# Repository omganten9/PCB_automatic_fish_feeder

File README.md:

# IoT-Based Automatic Fish Feeder System 🐟

An **IoT-integrated automatic fish feeder** designed using **ESP32** and **KiCad PCB design** to optimize aquarium maintenance.  
This project was developed as part of the *Final Project RE 2* course at Universitas Indonesia (2023).

---

## 🧠 Overview
This system enables automated and remote control of fish feeding using IoT technology.  
With motion and turbidity sensors, the feeder intelligently manages feeding schedules, monitors water conditions, and communicates through a **web server** via **Wi-Fi**.

**Key features:**
- Remote feeding schedule control via web interface  
- Real-time water turbidity monitoring  
- OLED/LCD display showing feeding status and last feeding time  
- Owner confirmation before auto-feeding for security  
- Deep sleep mode for efficient power usage  

---

## ⚙️ Hardware Summary
- **Microcontroller:** ESP32  
- **Sensors:** PIR (motion) sensor, turbidity sensor  
- **Actuators:** Servo motor (feeding mechanism), buzzer  
- **Display:** OLED / LCD  
- **Power System:** TP4056 Li-Ion charger module, 3.7V Li-ion battery  
- **Interfaces:** UART, USB Type-C (CP2104), Wi-Fi (Web Server)  

---

## 🧩 PCB Design
The PCB was designed using **KiCad** with:
- Dual-layer copper traces (signal + ground)  
- Ground filling for noise reduction and EMI suppression  
- Proper antenna clearance for ESP32 Wi-Fi module  
- Mounting holes for mechanical stability  
- Compact design for integration inside an aquarium enclosure  

---

## 🧰 Components Used
| Category | Components |
|-----------|-------------|
| Microcontroller | ESP32 |
| Sensors | PIR, Turbidity Sensor |
| Display | OLED/LCD |
| Actuators | Servo Motor, Buzzer |
| Power | TP4056, Li-ion Battery |
| Communication | CP2104 USB to UART, Wi-Fi |

---

## 📐 PCB Layout (Example)  

---

## 🧾 Author & Contribution
**Team 8 – Final Project RE 2 (Universitas Indonesia, 2023)**  
- **M. Akmal Prabowo** – Schematic & PCB Design, Report (Results & Discussion)  
- **M. Daffa Zainal** – Schematic Documentation  
- **Salman Hakim Kurnia** – Feature & Component Design, Ideation, Video Editing  

---

## 📚 Reference
Full report: *Final Project RE 2 – IoT-Based Automatic Fish Feeder System (Universitas Indonesia, 2023)*  
YouTube Demo: [https://www.youtube.com/watch?v=FHcyZINsoDI](https://www.youtube.com/watch?v=FHcyZINsoDI)

---

## 📜 License
This project is for **educational and personal portfolio use only**.  
Commercial reproduction or redistribution is not permitted.

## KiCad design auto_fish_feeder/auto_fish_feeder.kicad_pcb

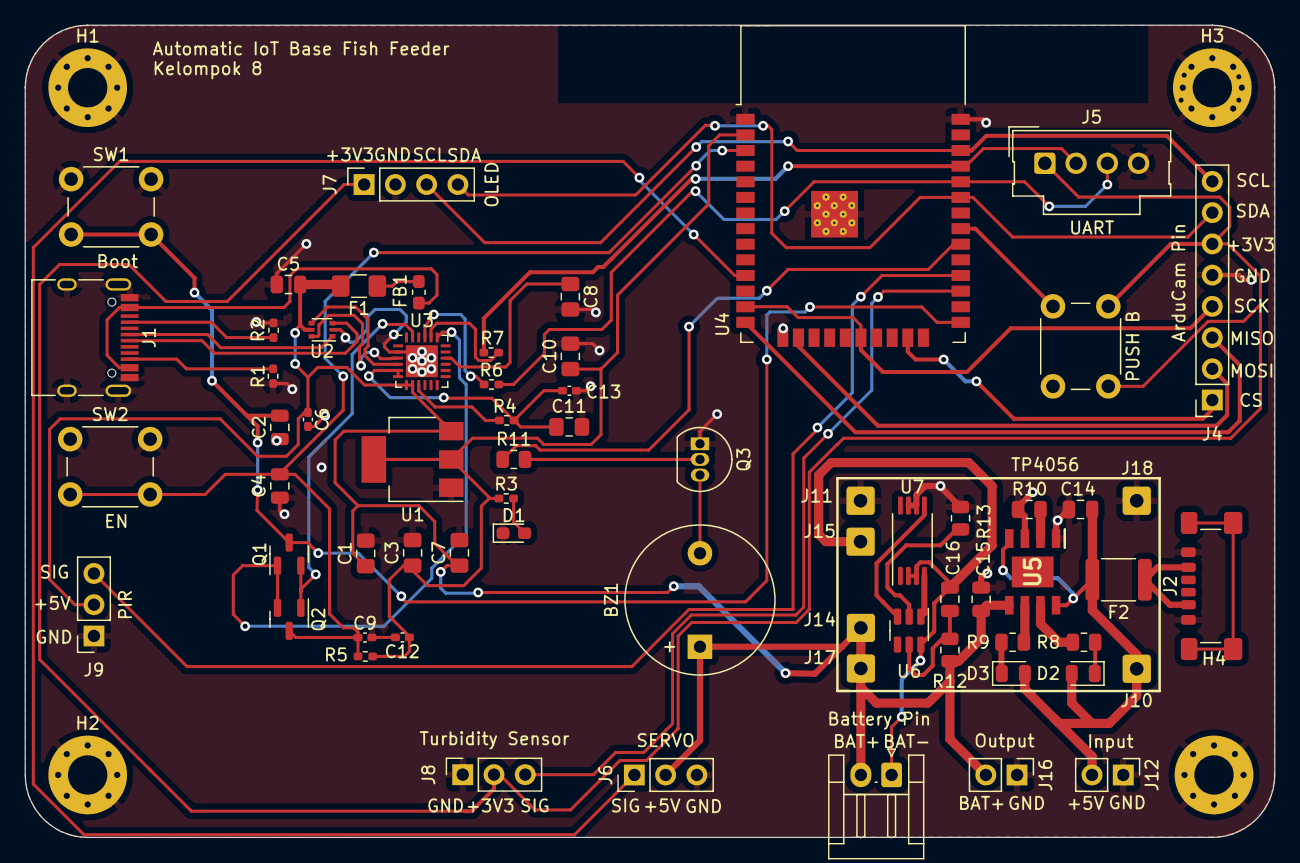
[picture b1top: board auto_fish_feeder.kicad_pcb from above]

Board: 2 copper layers, 101.6 x 66.0 mm, 70 parts (0 on the bottom side), 49 nets.

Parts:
BZ1: Buzzer; Buzzer_12x9.5RM7.6
C1, C3, C10, C11: 22u; C_0805_2012Metric_Pad1.18x1.45mm_HandSolder
C2, C4: 0.1uF/50V(10%); C_0805_2012Metric
C5: 22u; C_0805_2012Metric
C6, C9, C12, C13: 100n; C_0402_1005Metric_Pad0.74x0.62mm_HandSolder
C7, C8: 4u7; C_0805_2012Metric_Pad1.18x1.45mm_HandSolder
C14, C15: 10uF; C_0805_2012Metric
C16: 0.1uF; C_0805_2012Metric
D1: GREEN; LED_0603_1608Metric_Pad1.05x0.95mm_HandSolder
D2: Red; LED_0805_2012Metric
D3: Green; LED_0805_2012Metric
F1: Polyfuse 1A; Fuse_1206_3216Metric_Pad1.42x1.75mm_HandSolder
F2: Fuse; Fuse_1812_4532Metric
FB1: BLM21PG221; L_0603_1608Metric_Pad1.05x0.95mm_HandSolder
H1, H2, H3, H4: Hole_Pad; MountingHole_3.2mm_M3_Pad_Via
J1: USB_C_Receptacle_USB2.0; USB_C_Receptacle_HRO_TYPE-C-31-M-12
J2: USB_C_Receptacle_PowerOnly_6P; USB_C_Receptacle_GCT_USB4135-GF-A_6P_TopMnt_Horizontal
J4: Camera pin; PinSocket_1x08_P2.54mm_Vertical
J5: UART; Molex_SL_171971-0004_1x04_P2.54mm_Vertical
J6: SERVO; PinHeader_1x03_P2.54mm_Vertical
J7: OLED; PinSocket_1x04_P2.54mm_Vertical
J8: Turbidity Sensor; PinSocket_1x03_P2.54mm_Vertical
J9: PIR; PinSocket_1x03_P2.54mm_Vertical
J10: VBus; SolderWire-0.5sqmm_1x01_D0.9mm_OD2.3mm
J11, J18: GND; SolderWire-0.5sqmm_1x01_D0.9mm_OD2.3mm
J12: Input; PinHeader_1x02_P2.54mm_Vertical
J13: Battery Pin; JST_EH_S2B-EH_1x02_P2.50mm_Horizontal
J14, J17: BAT+; SolderWire-0.5sqmm_1x01_D0.9mm_OD2.3mm
J15: BAT-; SolderWire-0.5sqmm_1x01_D0.9mm_OD2.3mm
J16: Output; PinHeader_1x02_P2.54mm_Vertical
PUSH B: SW_Push; SW_PUSH_6mm_H13mm
Q1, Q2: BC847; SOT-23
Q3: S8050; TO-92_Inline
R1, R2: 5K1; R_0402_1005Metric_Pad0.72x0.64mm_HandSolder
R3: 1K; R_0402_1005Metric_Pad0.72x0.64mm_HandSolder
R4, R5: 10K; R_0402_1005Metric_Pad0.72x0.64mm_HandSolder
R6, R7: 22R; R_0402_1005Metric_Pad0.72x0.64mm_HandSolder
R8, R9, R13: 1k; R_0805_2012Metric
R10: 1.2K; R_0805_2012Metric
R11: 470; R_0805_2012Metric
R12: 100; R_0805_2012Metric
SW1: Boot; SW_PUSH_6mm_H13mm
SW2: EN; SW_PUSH_6mm_H13mm
U1: TLV1117LV-3.3; SOT-223-3_TabPin2
U2: USBLC6-2P6; SOT-666
U3: CP2104; QFN-24-1EP_4x4mm_P0.5mm_EP2.6x2.6mm
U4: ESP32-WROOM-32D
U5: TP4056; SOIC127P600X175-9N
U6: DW01; SOT-23-6
U7: FS8205A; TSSOP-8_4.4x3mm_P0.65mm

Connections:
+3.3V: C3.1, C10.1, C12.1, R3.1, R5.1, U1.2 (VO), U4.2 (VDD)
+3.3VA: C11.1, C13.1, R4.1, U3.5 (VIO), U3.6 (VDD)
+3V3: J4.6, J5.1, J7.1, J8.2, PUSH B.1
+5V: BZ1.1 (-), C1.1, C5.1, C6.1, C7.1, C15.1, F1.2, J6.2, J9.2, J13.2, J14.1, J16.2, J17.1, R12.1, U1.3 (VI), U2.5 (VBUS), U3.7 (REGIN), U3.8 (VBUS), U5.5 (BAT)
+5VP: FB1.1, J1.A4 (VBUS), J1.A9 (VBUS), J1.B4 (VBUS), J1.B9 (VBUS)
/BAT-: C16.1, J13.1, J15.1, U6.6 (GND), U7.2 (S1), U7.3 (S1)
/BUZZER: R11.1, U4.30 (IO18)
/CS: J4.1, U4.23 (IO15)
/DTR: Q1.2 (E), Q2.1 (B), U3.23 (~DTR)
/EN: C4.2, C9.1, Q2.3 (C), R5.2, SW2.2, U4.3 (EN)
/ESP_GPIO16: J8.3, U4.27 (IO16)
/ESP_GPIO17: J9.3, U4.28 (IO17)
/ESP_GPIO19: PUSH B.2, U4.31 (IO19)
/IO0: C2.2, Q1.3 (C), SW1.2, U4.25 (IO0)
/MISO: J4.3, U4.14 (IO12)
/MOSI: J4.2, U4.16 (IO13)
/RTS: Q1.1 (B), Q2.2 (E), U3.19 (~RTS)
/RX: J5.3, R6.2, U4.34 (RXD0/IO3)
/SCK: J4.4, U4.13 (IO14), U4.20 (SCK/CLK)
/SCL: J4.8, J7.3, U4.36 (IO22)
/SDA: J4.7, J7.4, U4.33 (IO21)
/SERVO: J6.1, U4.11 (IO26)
/TX: J5.2, R7.2, U4.35 (TXD0/IO1)
/VBUS: C14.1, D2.2 (A), D3.2 (A), F2.2, J10.1, J12.2, U5.4 (VCC), U5.8 (CE)
GND: C1.2, C2.1, C3.2, C4.1, C5.2, C6.2, C7.2, C8.2, C9.2, C10.2, C11.2, C12.2, C13.2, C14.2, C15.2, D1.1 (K), H1.1, H2.1, H3.1, H4.1, J1.A1 (GND), J1.A12 (GND), J1.B1 (GND), J1.B12 (GND), J1.S1 (SHIELD), J2.A12 (GND), J2.B12 (GND), J4.5, J5.4, J6.3, J7.2, J8.1, J9.1, J11.1, J12.1, J16.1, J18.1, Q3.1 (E), R1.2, R2.2, R10.2, R13.2, SW1.1, SW2.1, U1.1 (GND), U2.2 (GND), U3.2 (GND), U3.25 (GND), U4.1 (GND), U4.15 (GND), U4.38 (GND), U4.39 (GND), U5.1 (TEMP), U5.3 (GND), U7.6 (S2), U7.7 (S2)
unnamed: BZ1.2 (+), Q3.3 (C)
unnamed: D1.2 (A), R3.2
unnamed: D2.1 (K), R8.1
unnamed: D3.1 (K), R9.2
unnamed: F1.1, FB1.2
unnamed: F2.1, J2.A9 (VBUS), J2.B9 (VBUS)
unnamed: J1.A5 (CC1), R2.1
unnamed: J1.B5 (CC2), R1.1
unnamed: J1.A6 (D+), J1.B6 (D+), U2.1 (I/O1)
unnamed: J1.A7 (D-), J1.B7 (D-), U2.3 (I/O2)
unnamed: Q3.2 (B), R11.2
unnamed: U2.6 (I/O1), U3.3 (D+)
unnamed: U2.4 (I/O2), U3.4 (D-)
unnamed: R7.1, U3.20 (RXD)
unnamed: R6.1, U3.21 (TXD)
unnamed: C8.1, U3.16 (VPP)
unnamed: R4.2, U3.9 (~RST)
unnamed: R10.1, U5.2 (PROG)
unnamed: R8.2, U5.7 (~CHRG)
unnamed: R9.1, U5.6 (~STDBY)
unnamed: R13.1, U6.2 (CS)
unnamed: U6.3 (OC), U7.5 (G2)
unnamed: U6.1 (OD), U7.4 (G1)
unnamed: C16.2, R12.2, U6.5 (VCC)

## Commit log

2025-11-25 Create temp
